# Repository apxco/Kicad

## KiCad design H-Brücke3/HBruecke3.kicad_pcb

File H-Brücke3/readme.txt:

Version der H-Brücke2 mit nebeneinanderleigenden Leistungstransistoren

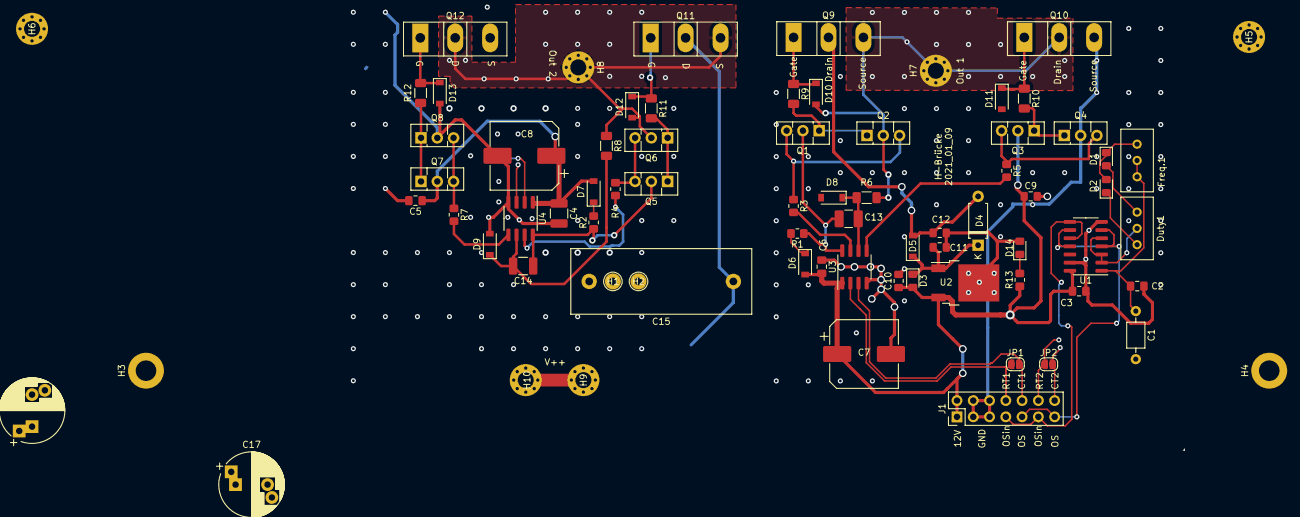
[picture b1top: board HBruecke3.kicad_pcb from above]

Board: 2 copper layers, 75 parts (0 on the bottom side), 40 nets.

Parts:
C1: 100n; C_Axial_L3.8mm_D2.6mm_P7.50mm_Horizontal
C2: 100n; C_0805_2012Metric_Pad1.18x1.45mm_HandSolder
C3, C5, C6: 100nF; C_0805_2012Metric_Pad1.18x1.45mm_HandSolder
C4, C14: 10uF; C_1210_3225Metric_Pad1.33x2.70mm_HandSolder
C7, C8: 100uF; CP_Elec_10x10.5
C9, C11, C12: 100nF; C_0805_2012Metric_Pad1.15x1.40mm_HandSolder
C10: 1uF; C_0805_2012Metric_Pad1.15x1.40mm_HandSolder
C13: 10uF; C_1210_3225Metric_Pad1.42x2.65mm_HandSolder
C15: 10uF; C_Rect_L28.0mm_W10.0mm_P22.50mm_MKS4
C16, C17: 100uF; CP_Radial_D10.0mm_P5.00mm_P7.50mm
D1, D2, D3: D; D_0805_2012Metric_Pad1.15x1.40mm_HandSolder
D4: D; D_A-405_P7.62mm_Horizontal
D5: D; D_SOD-123
D6, D7, D8, D9: D_Schottky; D_SOD-123
D10, D11, D12, D13: D_Zener; D_SOD-123
D14: LED; LED_0805_2012Metric_Pad1.15x1.40mm_HandSolder
Duty1: 1k; Potentiometer_Bourns_3296W_Vertical
Freq.1: 10k; Potentiometer_Bourns_3296W_Vertical
H1, H2: MountingHole_Pad; TestPoint_THTPad_D2.5mm_Drill1.2mm
H3, H4: MountingHole_Pad; MountingHole_3.2mm_M3_DIN965_Pad
H5, H6, H7, H8, H9, H10: MountingHole_Pad; MountingHole_2.5mm_Pad_Via
J1: Conn_02x07_Odd_Even; PinHeader_2x07_P2.54mm_Vertical
JP1, JP2: SolderJumper_2_Bridged; SolderJumper-2_P1.3mm_Open_RoundedPad1.0x1.5mm
Q1, Q3, Q5, Q7: BD139; TO-126-3_Vertical
Q2, Q4, Q6, Q8: BD140; TO-126-3_Vertical
Q9, Q10, Q11, Q12: C2M0025120D; TO-247-3_Vertical
R1, R2, R3, R4, R5, R7: 10R; R_0805_2012Metric_Pad1.20x1.40mm_HandSolder
R6, R8, R9, R10, R11, R12: 1R; R_1206_3216Metric_Pad1.30x1.75mm_HandSolder
R13: 10k; R_0805_2012Metric_Pad1.20x1.40mm_HandSolder
U1: 40106; SO-14_3.9x8.65mm_P1.27mm
U2: L7812; TO-252-2
U3, U4: U3115S; SOP-8_3.76x4.96mm_P1.27mm

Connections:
+12V: C3.1, C4.1, C5.1, C6.1, C7.1, C8.1, C9.1, C10.1, D3.2 (A), D6.2 (A), D7.2 (A), J1.1, J1.2, Q3.2 (C), Q7.2 (C), R13.1, U1.14 (VDD), U2.3 (OUT), U3.1 (VCC), U4.1 (VCC)
+36V: C12.1, C15.1, C16.1, C17.1, D4.2 (A), D5.2 (A), H9.1, H10.1, Q9.2 (D), Q11.2 (D)
CT1: J1.10, JP1.2 (B), U3.3 (LIN)
CT2: J1.14, JP2.2 (B), U4.3 (LIN)
GND: C1.2, C2.2, C3.2, C4.2, C5.2, C6.2, C7.2, C8.2, C9.2, C10.2, C11.2, C12.2, C15.2, C16.2, C17.2, D8.2 (A), D9.2 (A), D11.2 (A), D13.2 (A), D14.2 (A), H1.1, H2.1, H3.1, H4.1, H5.1, H6.1, J1.3, J1.4, J1.5, J1.6, Q4.2 (C), Q8.2 (C), Q10.3 (S), Q12.3 (S), U1.7 (VSS), U1.13, U2.2 (GND), U3.4 (COM), U4.4 (COM)
unnamed: C1.1, C2.1, Freq.1.2, Freq.1.3, U1.1
unnamed: D1.2 (A), Duty1.3
unnamed: D1.1 (K), D2.2 (A), Freq.1.1
unnamed: D2.1 (K), Duty1.1
unnamed: C11.1, D3.1 (K), D4.1 (K), D5.1 (K), U2.1 (IN)
unnamed: D6.1 (K), R1.2
unnamed: D7.1 (K), R2.2
unnamed: C13.2, D8.1 (K), R6.2, U3.6 (VS)
unnamed: C14.2, D9.1 (K), R8.2, U4.6 (VS)
unnamed: D10.2 (A), H7.1, Q2.2 (C), Q9.3 (S), Q10.2 (D), R6.1
unnamed: D10.1 (K), Q9.1 (G), R9.1
unnamed: D11.1 (K), Q10.1 (G), R10.1
unnamed: D12.2 (A), H8.1, Q6.2 (C), Q11.3 (S), Q12.2 (D), R8.1
unnamed: D12.1 (K), Q11.1 (G), R11.1
unnamed: D13.1 (K), Q12.1 (G), R12.1
unnamed: D14.1 (K), R13.2
unnamed: Duty1.2, U1.2, U1.3, U1.5
unnamed: Q1.3 (B), Q2.3 (B), R3.1
unnamed: C13.1, Q1.2 (C), R1.1, U3.8 (VB)
unnamed: Q1.1 (E), Q2.1 (E), R9.2
unnamed: Q3.3 (B), Q4.3 (B), R5.1
unnamed: Q3.1 (E), Q4.1 (E), R10.2
unnamed: Q5.3 (B), Q6.3 (B), R4.1
unnamed: C14.1, Q5.2 (C), R2.1, U4.8 (VB)
unnamed: Q5.1 (E), Q6.1 (E), R11.2
unnamed: Q7.3 (B), Q8.3 (B), R7.1
unnamed: Q7.1 (E), Q8.1 (E), R12.2
unnamed: R3.2, U3.7 (HO)
unnamed: R5.2, U3.5 (LO)
unnamed: R4.2, U4.7 (HO)
unnamed: R7.2, U4.5 (LO)
OSC_inv: J1.7, J1.11, U1.8, U1.10
Osc: J1.9, J1.13, U1.4, U1.6, U1.9, U1.11
RT1: J1.8, JP1.1 (A), U3.2 (HIN)
RT2: J1.12, JP2.1 (A), U4.2 (HIN)

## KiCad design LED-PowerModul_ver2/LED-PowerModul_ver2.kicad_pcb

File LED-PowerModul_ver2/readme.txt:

Treiber für Power-LED mittlere Leistung

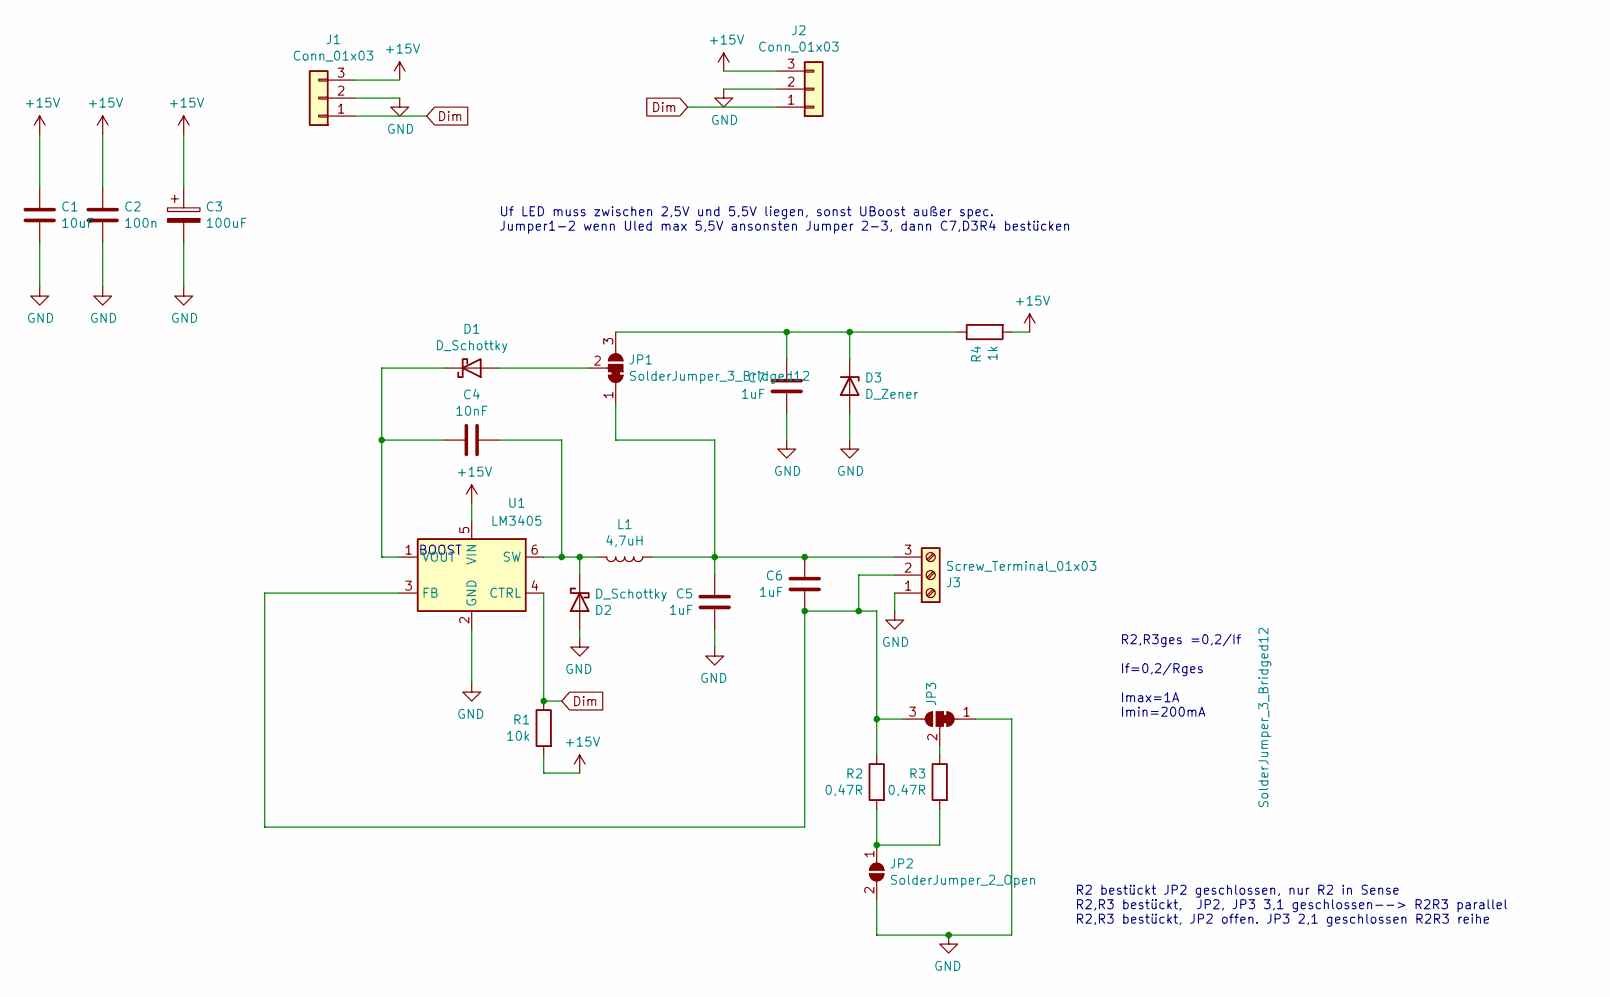
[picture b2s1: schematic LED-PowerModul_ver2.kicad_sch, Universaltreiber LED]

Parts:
C1: 10uF; C_0805_2012Metric_Pad1.15x1.40mm_HandSolder
C2: 100n; C_0805_2012Metric_Pad1.15x1.40mm_HandSolder
C3: 100uF; CP_Elec_6.3x5.9
C4: 10nF; C_0805_2012Metric_Pad1.15x1.40mm_HandSolder
C5, C6, C7: 1uF; C_0805_2012Metric_Pad1.15x1.40mm_HandSolder
D1, D2: D_Schottky; D_1806_4516Metric_Pad1.57x1.80mm_HandSolder
D3: D_Zener; D_1806_4516Metric_Pad1.57x1.80mm_HandSolder
J1, J2: Conn_01x03; PinSocket_1x03_P2.54mm_Vertical
J3: Screw_Terminal_01x03; PinSocket_1x03_P2.54mm_Vertical
JP1, JP3: SolderJumper_3_Bridged12; SolderJumper-3_P1.3mm_Bridged12_RoundedPad1.0x1.5mm_NumberL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
JP2: SolderJumper_2_Open; SolderJumper-2_P1.3mm_Open_Pad1.0x1.5mm
L1: 4,7uH; L_Murata_LQH55DN_5.7x5.0mm
R1: 10k; R_0805_2012Metric_Pad1.15x1.40mm_HandSolder
R2, R3: 0,47R; R_2512_6332Metric_Pad1.52x3.35mm_HandSolder
R4: 1k; R_0805_2012Metric_Pad1.15x1.40mm_HandSolder
U1: LM3405; TSOT-23-6

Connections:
+15V: C1.1, C2.1, C3.1, J1.3, J2.3, R1.2, R4.2, U1.5 (VIN)
Dim: J1.1, J2.1, R1.1, U1.4 (CTRL)
GND: C1.2, C2.2, C3.2, C5.2, C7.2, D2.2 (A), D3.2 (A), J1.2, J2.2, J3.1, JP2.2 (B), JP3.1 (A), U1.2 (GND)
unnamed: C4.1, D2.1 (K), L1.1, U1.6 (SW)
unnamed: C4.2, D1.1 (K), U1.1 (VOUT)
unnamed: C5.1, C6.1, J3.3, JP1.1 (A), L1.2
unnamed: C6.2, J3.2, JP3.3 (B), R2.1, U1.3 (FB)
unnamed: C7.1, D3.1 (K), JP1.3 (B), R4.1
unnamed: D1.2 (A), JP1.2 (C)
unnamed: JP2.1 (A), R2.2, R3.2
unnamed: JP3.2 (C), R3.1

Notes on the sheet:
R2,R3ges =0,2/If If=0,2/Rges Imax=1A Imin=200mA
R2 bestückt JP2 geschlossen, nur R2 in Sense R2,R3 bestückt, JP2, JP3 3,1 geschlossen--> R2R3 parallel R2,R3 bestückt, JP2 offen. JP3 2,1 geschlossen R2R3 reihe
Uf LED muss zwischen 2,5V und 5,5V liegen, sonst UBoost außer spec. Jumper1-2 wenn Uled max 5,5V ansonsten Jumper 2-3, dann C7,D3R4 bestücken
BOOST

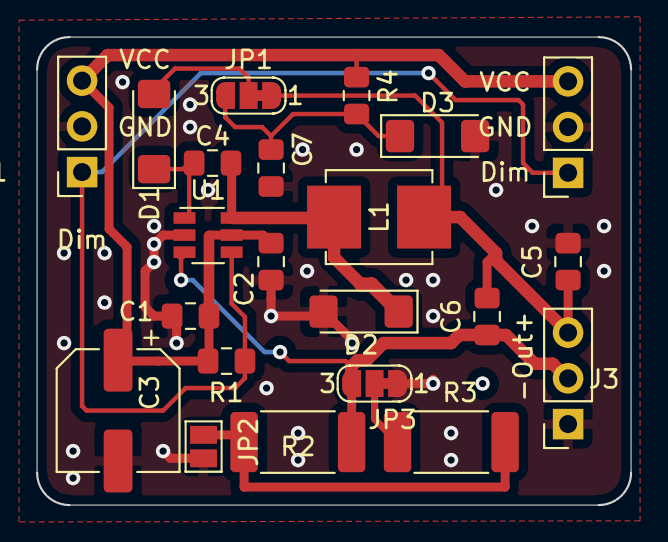
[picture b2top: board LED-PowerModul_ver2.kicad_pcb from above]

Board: 2 copper layers, 33.0 x 26.0 mm, 22 parts (0 on the bottom side), 11 nets.

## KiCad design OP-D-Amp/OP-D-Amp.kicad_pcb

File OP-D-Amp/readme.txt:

Experimenteller Modulator für Klasse D Verstärker.  

Letzte Version mit Anpassung der Werte, funktioniert soweit.

Werde sehen ob ich an diesem Projekt weiter mache. Ein integrierte Chip Lösung ist sicher zu bevorzugen.

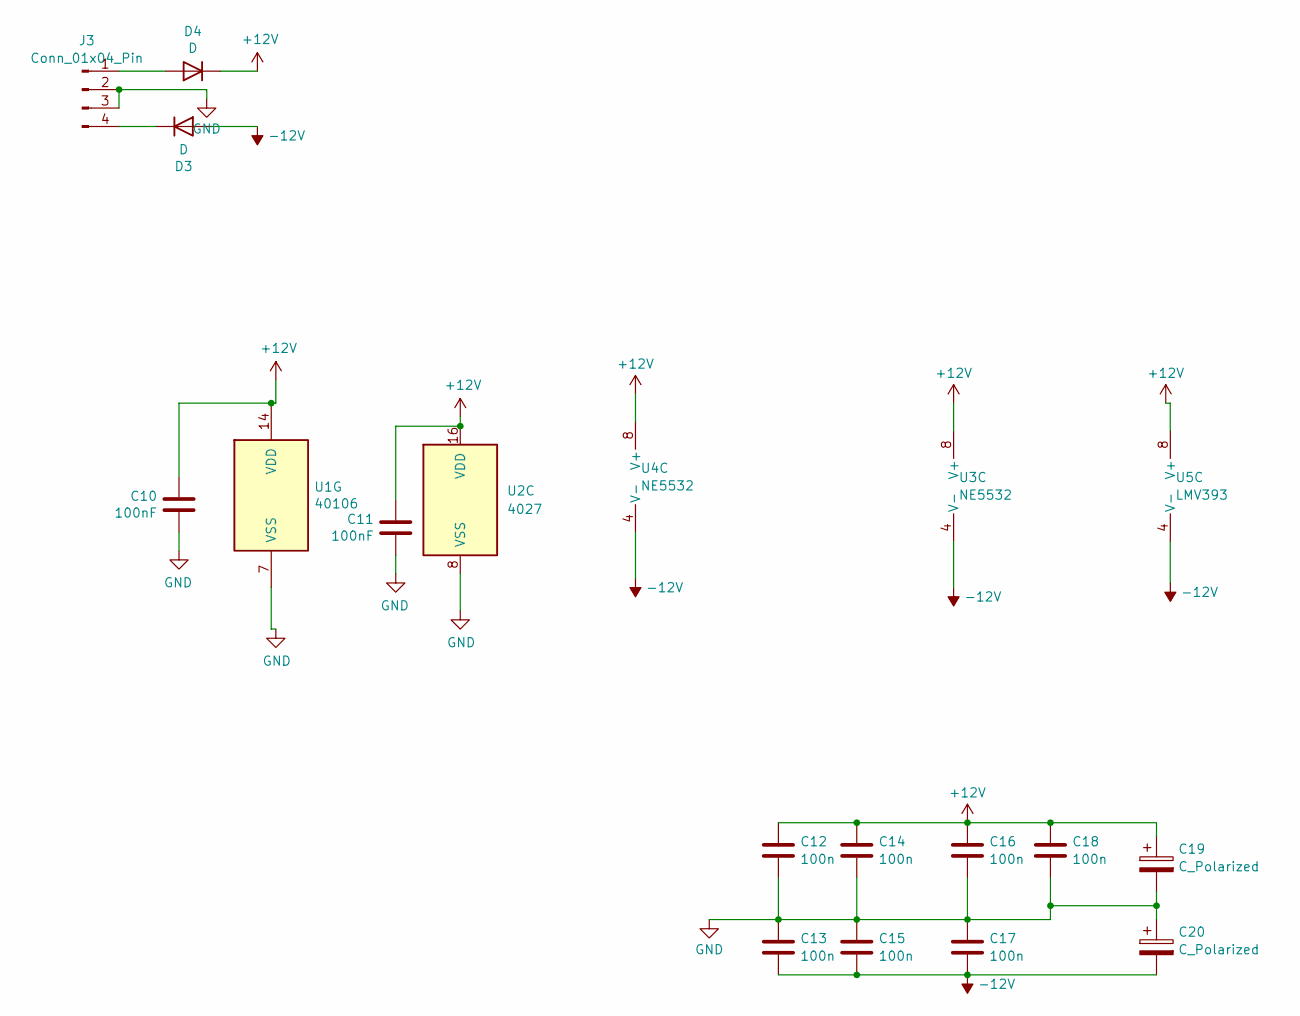
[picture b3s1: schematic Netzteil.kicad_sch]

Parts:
C10, C11: 100nF; C_0805_2012Metric_Pad1.18x1.45mm_HandSolder
C12, C13, C14, C15, C16, C17, C18: 100n; C_0805_2012Metric_Pad1.18x1.45mm_HandSolder
C19, C20: C_Polarized; CP_Radial_D8.0mm_P5.00mm
D3, D4: D; D_DO-35_SOD27_P7.62mm_Horizontal
J3: Conn_01x04_Pin; PinHeader_1x04_P2.54mm_Vertical
U1: 40106; SO-14_3.9x8.65mm_P1.27mm
U2: 4027; SOIC-16_3.9x9.9mm_P1.27mm
U3, U4: NE5532; SOP-8_3.76x4.96mm_P1.27mm
U5: LMV393; SOP-8_3.76x4.96mm_P1.27mm

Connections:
+12V: C10.1, C11.1, C12.2, C14.2, C16.2, C18.2, C19.1, D4.1 (K), U1.14 (VDD), U2.16 (VDD), U3.8 (V+), U4.8 (V+), U5.8 (V+); also elsewhere on the board
-12V: C13.1, C15.1, C17.1, C20.2, D3.2 (A), U3.4 (V-), U4.4 (V-), U5.4 (V-)
GND: C10.2, C11.2, C12.1, C13.2, C14.1, C15.2, C16.1, C17.2, C18.1, C19.2, C20.1, J3.2, J3.3, U1.7 (VSS), U2.8 (VSS); also elsewhere on the board
unnamed: D3.1 (K), J3.4
unnamed: D4.2 (A), J3.1

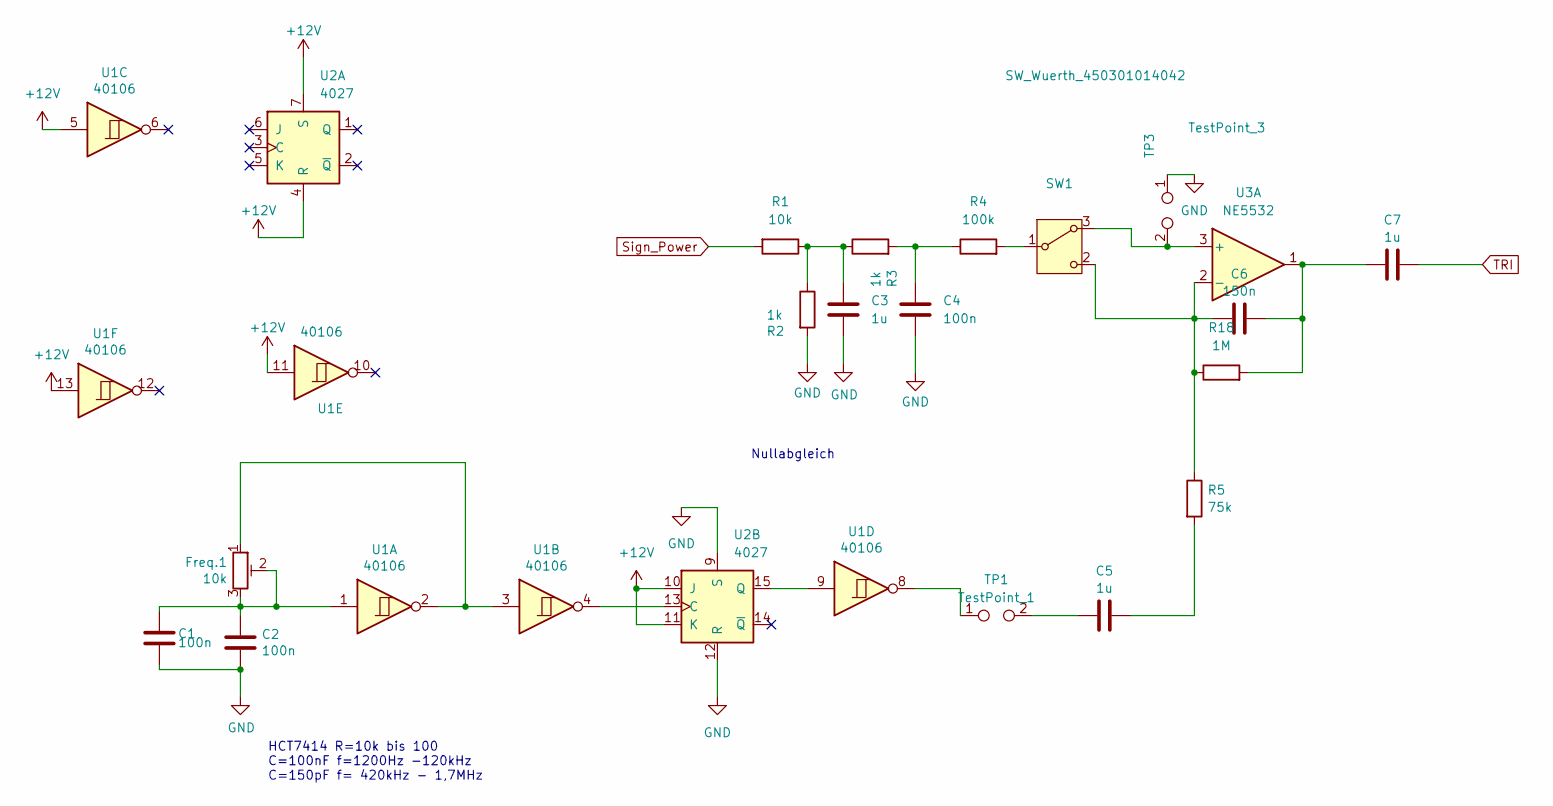
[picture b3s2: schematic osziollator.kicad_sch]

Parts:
C1: 100n; C_Axial_L3.8mm_D2.6mm_P7.50mm_Horizontal
C2, C4: 100n; C_0805_2012Metric_Pad1.18x1.45mm_HandSolder
C3: 1u; C_0805_2012Metric_Pad1.18x1.45mm_HandSolder
C5, C7: 1u; C_Axial_L3.8mm_D2.6mm_P7.50mm_Horizontal
C6: 150n; C_Axial_L3.8mm_D2.6mm_P7.50mm_Horizontal
Freq.1: 10k; Potentiometer_Bourns_3296W_Vertical
R1: 10k; R_0805_2012Metric_Pad1.20x1.40mm_HandSolder
R2, R3: 1k; R_0805_2012Metric_Pad1.20x1.40mm_HandSolder
R4: 100k; R_0805_2012Metric_Pad1.20x1.40mm_HandSolder
R5: 75k; R_0805_2012Metric_Pad1.20x1.40mm_HandSolder
R18: 1M; R_0805_2012Metric_Pad1.20x1.40mm_HandSolder
SW1: SW_Wuerth_450301014042; SW_Slide-03_Wuerth-WS-SLTV_10x2.5x6.4_P2.54mm
TP1: TestPoint_1; PinHeader_1x02_P2.54mm_Vertical
TP3: TestPoint_3; PinHeader_1x02_P2.54mm_Vertical
U1: 40106; SO-14_3.9x8.65mm_P1.27mm
U2: 4027; SOIC-16_3.9x9.9mm_P1.27mm
U3: NE5532; SOP-8_3.76x4.96mm_P1.27mm

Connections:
+12V: U1.5, U1.11, U1.13, U2.4 (R), U2.7 (S), U2.10 (J), U2.11 (K); also elsewhere on the board
GND: C1.2, C2.2, C3.2, C4.1, R2.2, TP3.1, U2.9 (S), U2.12 (R); also elsewhere on the board
unnamed: C1.1, C2.1, Freq.1.2, Freq.1.3, U1.1
unnamed: C3.1, R1.1, R2.1, R3.1
unnamed: C4.2, R3.2, R4.1
unnamed: C5.1, TP1.2
unnamed: C5.2, R5.2
unnamed: C6.2, C7.1, R18.2, U3.1
unnamed: Freq.1.1, U1.2, U1.3
unnamed: SW1.3 (A), TP3.2, U3.3 (+)
unnamed: R4.2, SW1.1 (B)
unnamed: C6.1, R5.1, R18.1, SW1.2 (C), U3.2 (-)
unnamed: TP1.1, U1.8
unnamed: U1.4, U2.13 (C)
unnamed: U1.9, U2.15 (Q)
Sign_Power: R1.2; also elsewhere on the board
TRI: C7.2; also elsewhere on the board

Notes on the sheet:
Nullabgleich
HCT7414 R=10k bis 100 C=100nF f=1200Hz -120kHz C=150pF f= 420kHz - 1,7MHz

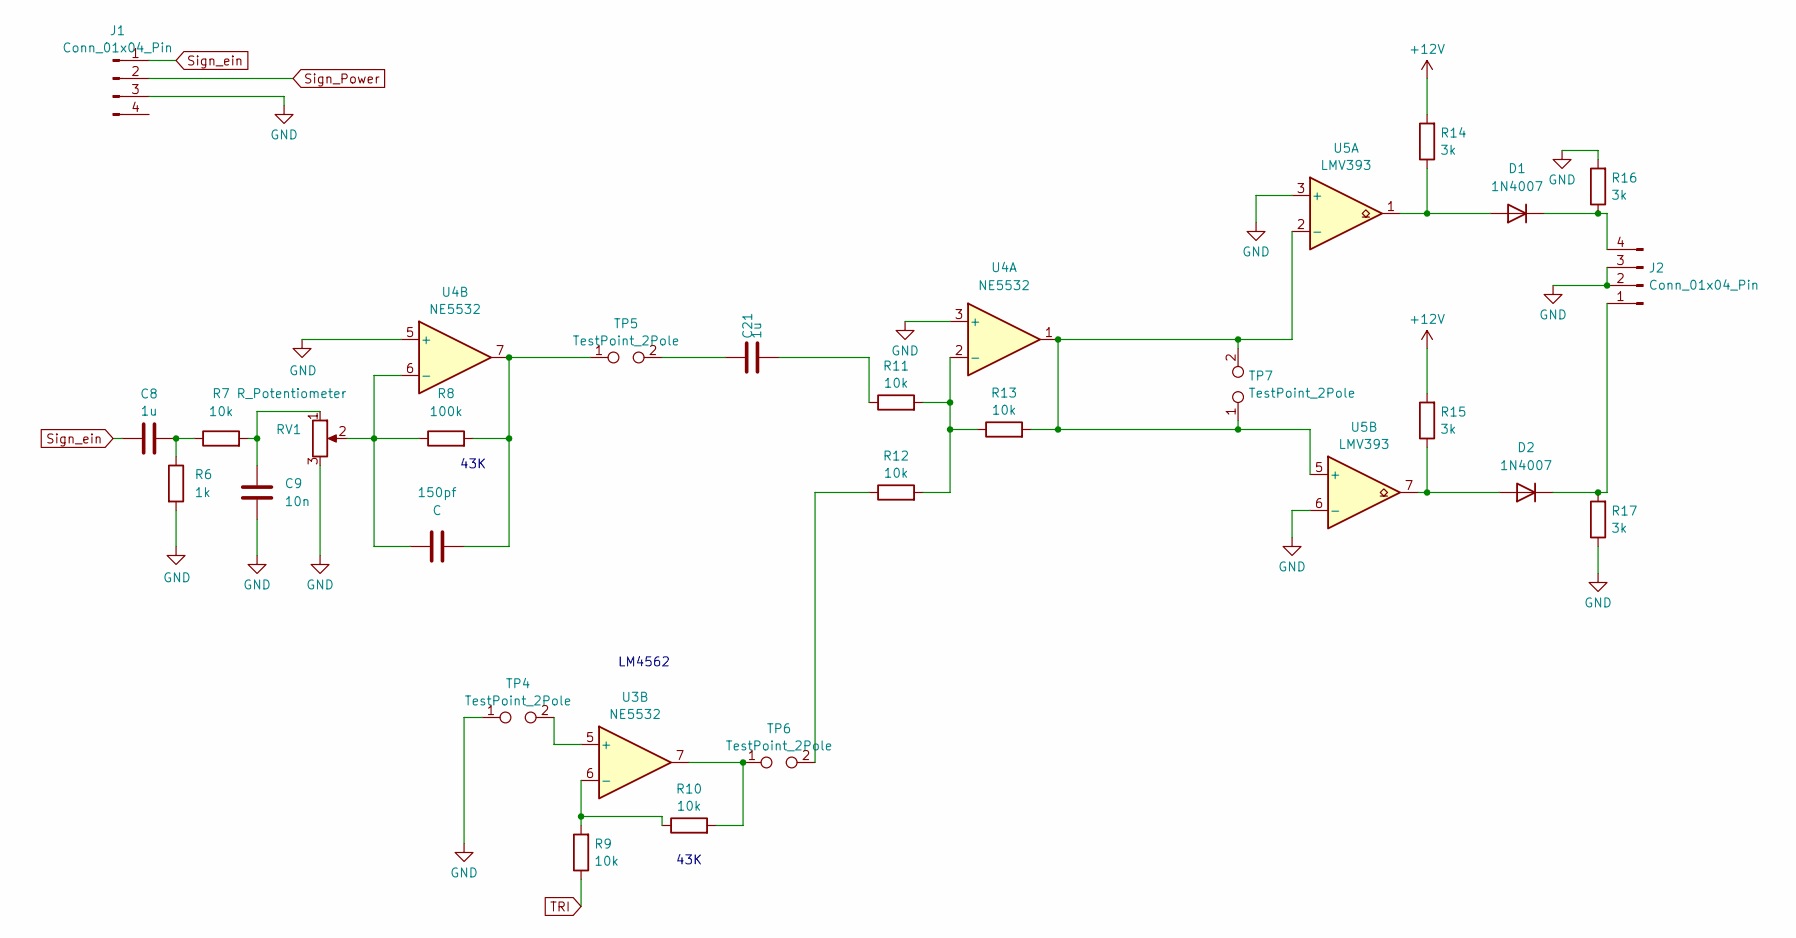
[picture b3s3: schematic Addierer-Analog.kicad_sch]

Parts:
150pf: C
C8, C21: 1u; C_Axial_L3.8mm_D2.6mm_P7.50mm_Horizontal
C9: 10n; C_0805_2012Metric_Pad1.18x1.45mm_HandSolder
D1, D2: 1N4007; D_DO-35_SOD27_P7.62mm_Horizontal
J1, J2: Conn_01x04_Pin; PinHeader_1x04_P2.54mm_Vertical
R6: 1k; R_0805_2012Metric_Pad1.20x1.40mm_HandSolder
R7, R9, R10, R11, R12, R13: 10k; R_0805_2012Metric_Pad1.20x1.40mm_HandSolder
R8: 100k; R_0805_2012Metric_Pad1.20x1.40mm_HandSolder
R14, R15, R16, R17: 3k; R_0805_2012Metric_Pad1.20x1.40mm_HandSolder
RV1: R_Potentiometer; Potentiometer_Alps_RK09K_Single_Vertical
TP4, TP5, TP6, TP7: TestPoint_2Pole; PinHeader_1x02_P2.54mm_Vertical
U3, U4: NE5532; SOP-8_3.76x4.96mm_P1.27mm
U5: LMV393; SOP-8_3.76x4.96mm_P1.27mm

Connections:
+12V: R14.2, R15.2; also elsewhere on the board
GND: C9.1, J1.3, J2.2, J2.3, R6.2, R16.2, R17.1, RV1.3, TP4.1, U4.3 (+), U4.5 (+), U5.3 (+), U5.6 (-); also elsewhere on the board
unnamed: C8.2, R6.1, R7.1
unnamed: C9.2, R7.2, RV1.1
unnamed: C21.1, TP5.2
unnamed: C21.2, R11.1
unnamed: D1.2 (A), R14.1, U5.1
unnamed: D1.1 (K), J2.4, R16.1
unnamed: D2.2 (A), R15.1, U5.7
unnamed: D2.1 (K), J2.1, R17.2
unnamed: 150pf.2, R8.2, TP5.1, U4.7
unnamed: R10.2, TP6.1, U3.7
unnamed: R12.1, TP6.2
unnamed: TP4.2, U3.5 (+)
unnamed: R9.2, R10.1, U3.6 (-)
unnamed: R11.2, R12.2, R13.1, U4.2 (-)
unnamed: 150pf.1, R8.1, RV1.2, U4.6 (-)
unnamed: R13.2, TP7.1, TP7.2, U4.1, U5.2 (-), U5.5 (+)
OSC_inv: J1.4
Sign_Power: J1.2; also elsewhere on the board
Sign_ein: C8.1, J1.1
TRI: R9.1; also elsewhere on the board

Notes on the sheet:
LM4562
43K

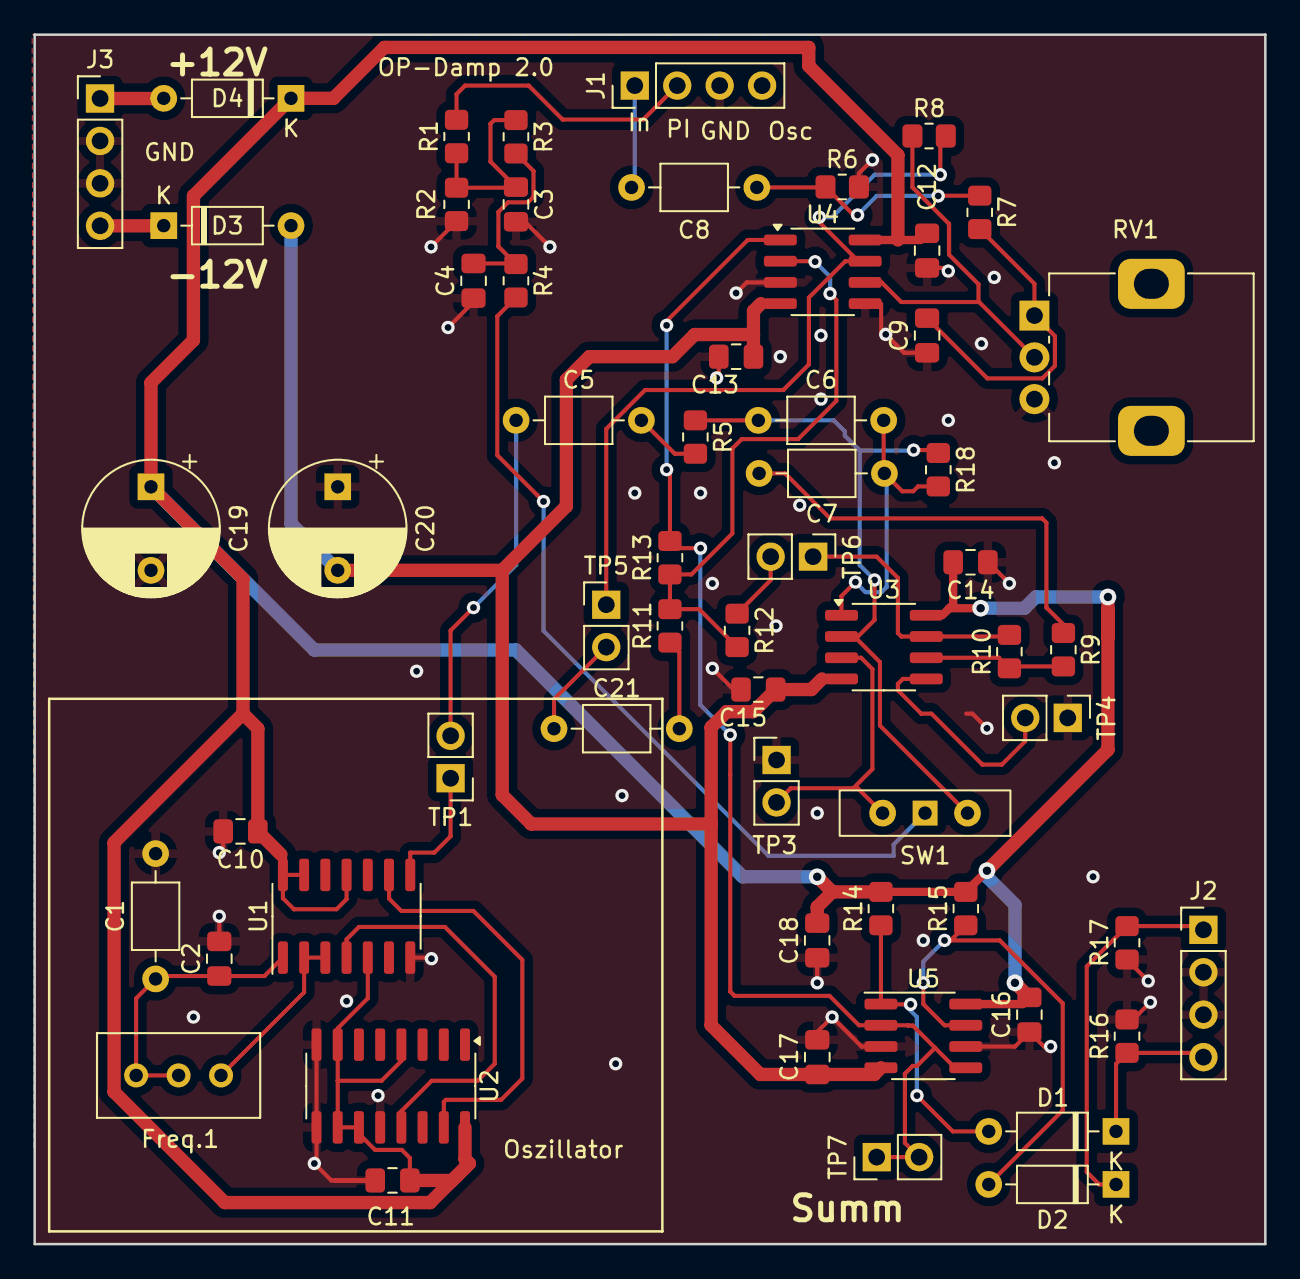
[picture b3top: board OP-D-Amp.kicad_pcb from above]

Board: 2 copper layers, 73.7 x 72.4 mm, 60 parts (0 on the bottom side), 37 nets.

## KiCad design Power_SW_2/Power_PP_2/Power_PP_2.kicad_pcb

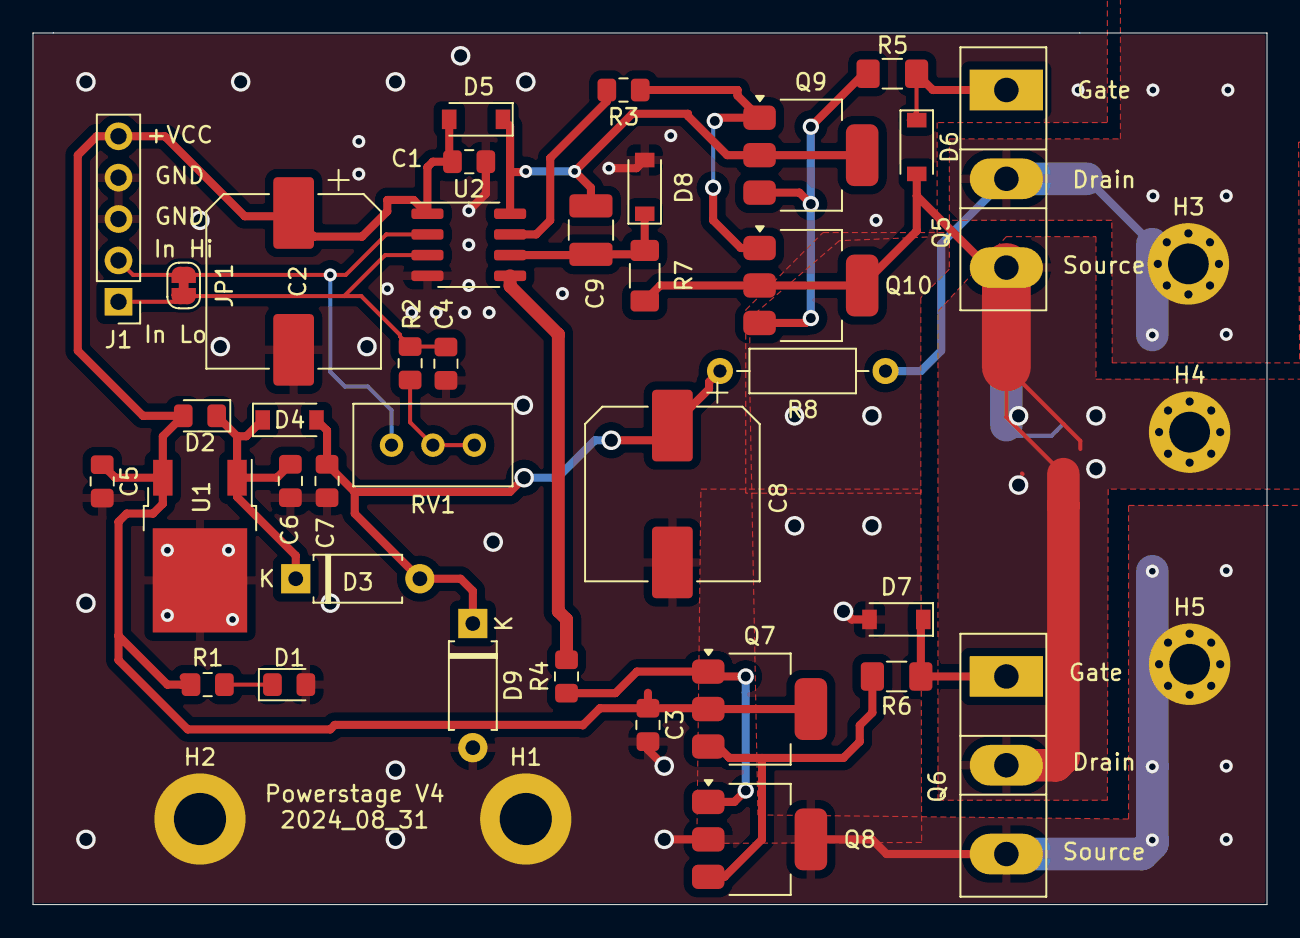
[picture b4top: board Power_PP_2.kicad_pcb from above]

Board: 2 copper layers, 75.8 x 53.5 mm, 42 parts (0 on the bottom side), 20 nets.

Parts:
C1, C3, C6, C7: 100nF; C_0805_2012Metric_Pad1.15x1.40mm_HandSolder
C2, C8: 100uF; CP_Elec_10x10.5
C4: C; C_0805_2012Metric_Pad1.15x1.40mm_HandSolder
C5: 1uF; C_0805_2012Metric_Pad1.15x1.40mm_HandSolder
C9: 10uF; C_1210_3225Metric_Pad1.42x2.65mm_HandSolder
D1: LED; LED_0805_2012Metric_Pad1.15x1.40mm_HandSolder
D2: D; D_0805_2012Metric_Pad1.15x1.40mm_HandSolder
D3: D; D_A-405_P7.62mm_Horizontal
D4: D; D_SOD-123
D5, D8: D_Schottky; D_SOD-123
D6, D7: D_Zener; D_SOD-123
D9: 24V-30V; D_A-405_P7.62mm_Horizontal
H1, H2: MountingHole_Pad; MountingHole_3.2mm_M3_DIN965_Pad
H3, H4, H5: MountingHole_Pad; MountingHole_2.5mm_Pad_Via
J1: Conn_01x05_Female; PinHeader_1x05_P2.54mm_Vertical
JP1: SolderJumper_2_Bridged; SolderJumper-2_P1.3mm_Bridged_RoundedPad1.0x1.5mm
Q5, Q6: C2M0025120D; TO-247-3_Vertical
Q7, Q9: FZT853; SOT-223-3_TabPin2
Q8, Q10: FZT953; SOT-223-3_TabPin2
R1: 10k; R_0805_2012Metric_Pad1.15x1.40mm_HandSolder
R2: R; R_0805_2012Metric_Pad1.15x1.40mm_HandSolder
R3, R4: 10R; R_0805_2012Metric_Pad1.15x1.40mm_HandSolder
R5, R6: 1R; R_1206_3216Metric_Pad1.42x1.75mm_HandSolder
R7: 1R; R_1206_3216Metric_Pad1.30x1.75mm_HandSolder
R8: 50R; R_Axial_DIN0207_L6.3mm_D2.5mm_P10.16mm_Horizontal
RV1: R_POT_TRIM; Potentiometer_Bourns_3296W_Vertical
U1: L7812; TO-252-2
U2: U3115S; SOP-8_3.76x4.96mm_P1.27mm

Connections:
+12V: C1.1, C2.1, C3.1, C5.1, D2.2 (A), D5.2 (A), J1.5, Q7.2 (C), R1.1, U1.3 (OUT), U2.1 (VCC)
+36V: H3.1, Q5.2 (D), R8.1
CT: C4.1, J1.1, JP1.2 (B), R2.2, U2.3 (LIN)
GND: C1.2, C2.2, C3.2, C4.2, C5.2, C6.2, C7.2, C8.2, D1.2 (A), D7.2 (A), D8.2 (A), D9.2 (A), H1.1, H2.1, H5.1, J1.3, J1.4, Q6.3 (S), Q8.2 (C), U1.2 (GND), U2.4 (COM)
unnamed: D1.1 (K), R1.2
unnamed: C6.1, D2.1 (K), D3.1 (K), D4.1 (K), U1.1 (IN)
unnamed: C7.1, C8.1, D3.2 (A), D4.2 (A), D9.1 (K), R8.2
unnamed: C9.1, D5.1 (K), Q9.2 (C), U2.8 (VB)
unnamed: D6.2 (A), H4.1, Q5.3 (S), Q6.2 (D), Q10.2 (C), R7.1
unnamed: D6.1 (K), Q5.1 (G), R5.1
unnamed: D7.1 (K), Q6.1 (G), R6.1
unnamed: C9.2, D8.1 (K), R7.2, U2.6 (VS)
unnamed: Q7.1 (B), Q8.1 (B), R4.1
unnamed: Q7.3 (E), Q8.3 (E), R6.2
unnamed: Q9.1 (B), Q10.1 (B), R3.1
unnamed: Q9.3 (E), Q10.3 (E), R5.2
unnamed: R2.1, RV1.2, RV1.3
unnamed: R3.2, U2.7 (HO)
unnamed: R4.2, U2.5 (LO)
RT: J1.2, JP1.1 (A), RV1.1, U2.2 (HIN)

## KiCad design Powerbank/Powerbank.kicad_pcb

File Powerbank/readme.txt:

Netzteil unreguliert mit großer Kondensatorbank.

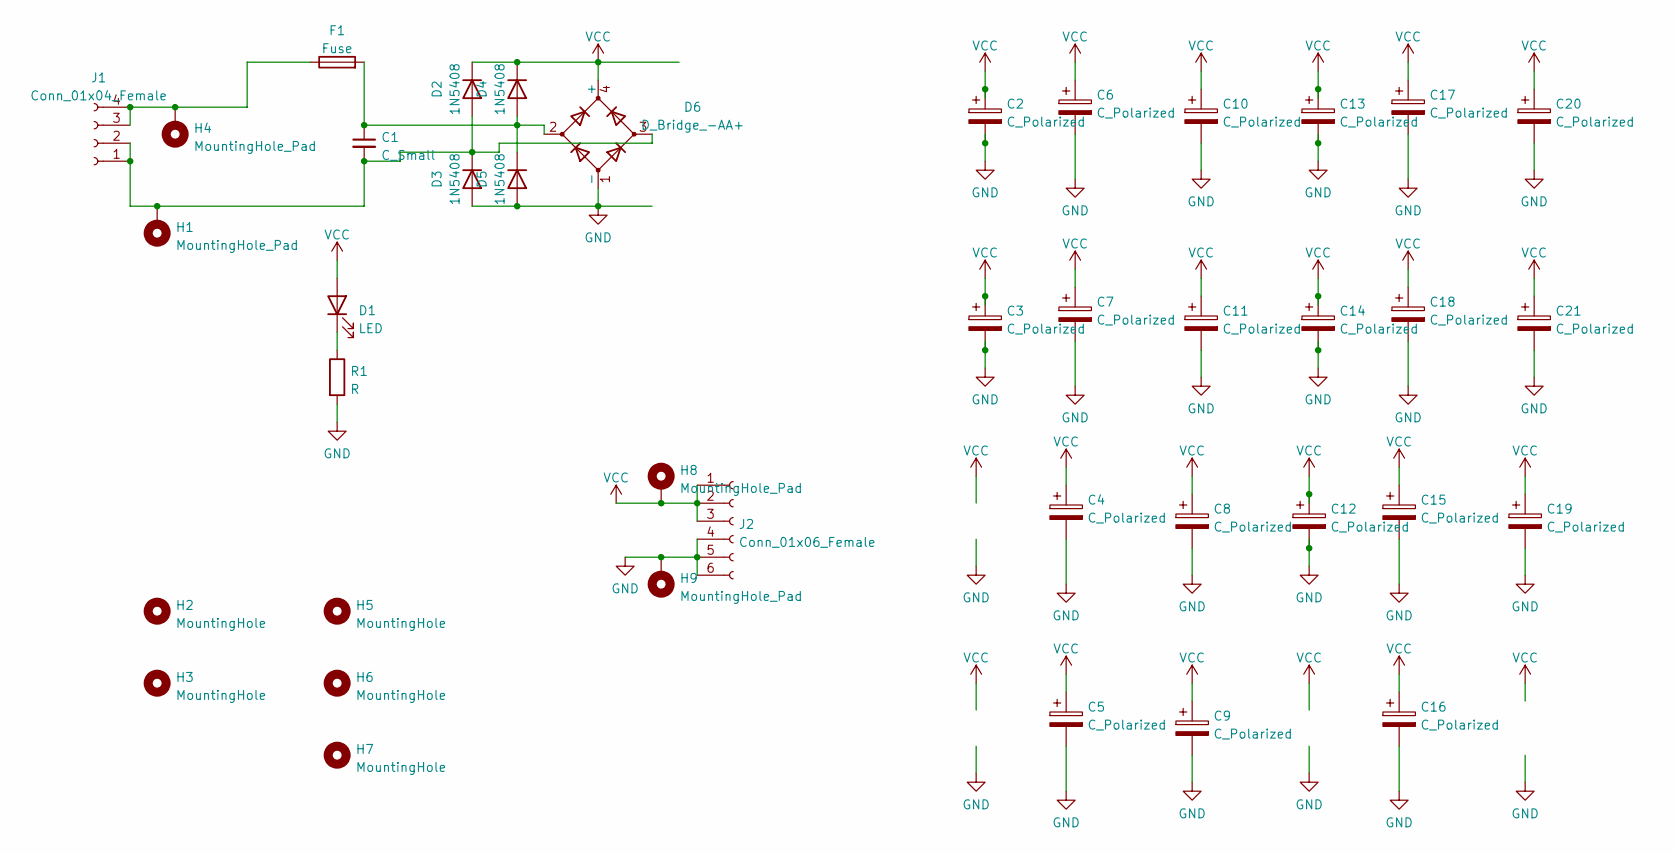
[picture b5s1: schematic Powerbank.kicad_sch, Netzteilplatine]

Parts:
C1: C_Small; C_Axial_L12.0mm_D6.5mm_P15.00mm_Horizontal
C2, C3, C4, C5, C6, C7, C8, C11, C12, C13, C14, C15, C16, C17, C18, C19: C_Polarized; CP_Radial_D12.5mm_P5.00mm
C9, C10, C20, C21: C_Polarized; C_Rect_L16.5mm_W5.0mm_P15.00mm_MKT
D1: LED; LED_D3.0mm_Clear
D2, D3, D4, D5: 1N5408; D_DO-201AD_P15.24mm_Horizontal
D6: D_Bridge_-AA+; Diode_Bridge_Vishay_GBU
F1: Fuse; Fuseholder_Littelfuse_100_series_5x20mm
H1, H4, H8, H9: MountingHole_Pad; MountingHole_3.2mm_M3_Pad_TopBottom
H2, H3, H5, H6, H7: MountingHole; MountingHole_3.5mm_Pad
J1: Conn_01x04_Female; PinHeader_1x04_P2.54mm_Vertical
J2: Conn_01x06_Female; PinHeader_1x06_P2.54mm_Vertical
R1: R; R_Axial_DIN0204_L3.6mm_D1.6mm_P7.62mm_Horizontal

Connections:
GND: C2.2, C3.2, C4.2, C5.2, C6.2, C7.2, C8.2, C9.2, C10.2, C11.2, C12.2, C13.2, C14.2, C15.2, C16.2, C17.2, C18.2, C19.2, C20.2, C21.2, D3.2 (A), D5.2 (A), D6.1 (-), H9.1, J2.4, J2.5, J2.6, R1.2
unnamed: C1.1, D4.2 (A), D5.1 (K), D6.2, F1.2
unnamed: C1.2, D2.2 (A), D3.1 (K), D6.3, H1.1, J1.1, J1.2
unnamed: D1.1 (K), R1.1
unnamed: F1.1, H4.1, J1.3, J1.4
VCC: C2.1, C3.1, C4.1, C5.1, C6.1, C7.1, C8.1, C9.1, C10.1, C11.1, C12.1, C13.1, C14.1, C15.1, C16.1, C17.1, C18.1, C19.1, C20.1, C21.1, D1.2 (A), D2.1 (K), D4.1 (K), D6.4 (+), H8.1, J2.1, J2.2, J2.3

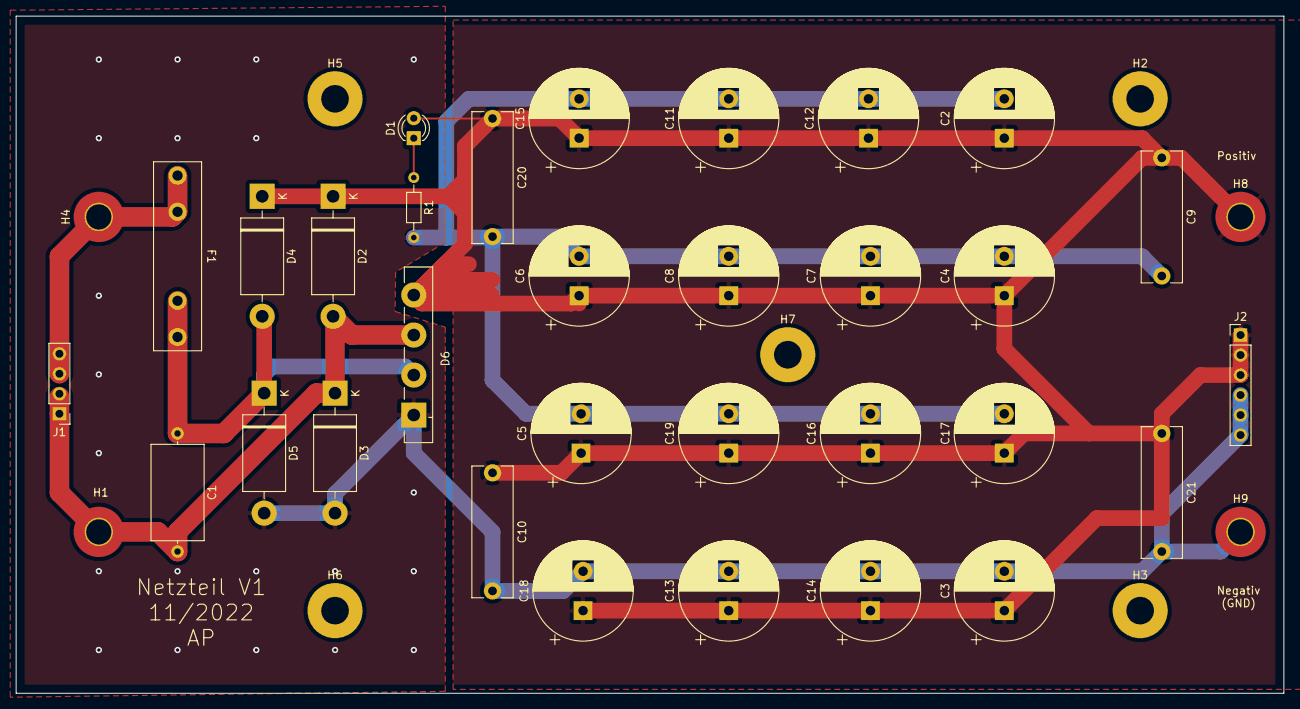
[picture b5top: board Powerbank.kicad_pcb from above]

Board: 2 copper layers, 161.0 x 86.0 mm, 40 parts (0 on the bottom side), 6 nets.
